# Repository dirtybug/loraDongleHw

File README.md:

# LoRa DualBand Hardware

R2 development draft. Not approved for manufacture. Hardware only; firmware and Android are separate submodules.

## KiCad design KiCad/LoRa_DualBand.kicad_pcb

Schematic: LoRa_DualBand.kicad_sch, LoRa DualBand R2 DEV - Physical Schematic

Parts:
C1A, C1B: 220u; C_1210_3225Metric; MPN GRM32ER60J227ME05L; not fitted
C2, C3, C4, C5, C6, C7, C9, C23, C25, C28, C35, C36, C37, C42, C44, C46, C48, C49, C50, C52, C53, C54, C55, C56, C59, C65, C66, C71, C73: 100n; C_0603_1608Metric; MPN CC0603KRX7R7BB104
C8, C32, C33, C34, C60, C63, C64: 1u; C_0603_1608Metric; MPN CC0603KRX7R6BB105
C10, C21, C38, C43, C45, C47, C51, C61: 4.7u; C_0603_1608Metric; MPN CC0603MRX5R6BB475
C20: 22n; C_0603_1608Metric; MPN CC0603KRX7R9BB223; not fitted
C22: 4.7u; C_0603_1608Metric; MPN CC0603MRX5R6BB475; not fitted
C24: 10u; C_0805_2012Metric; MPN GRM21BR61C106KE15L
C26, C27, C70, C72: 22u; C_0805_2012Metric; MPN GRM21BR61A226ME44L
C30, C31, C40, C41, C57, C58: 18p; C_0603_1608Metric; MPN CC0603JRNPO9BN180
C62: 1n; C_0603_1608Metric; MPN CC0603KRX7R9BB102
D1: USBLC6-2SC6; SOT-23-6; MPN USBLC6-2SC6
D2: SMAJ5.0A; D_SMA; MPN SMAJ5.0A
D3: SMAJ5.0A; D_SMA; MPN SMAJ5.0A; not fitted
FB1, FB2: 600R@100MHz; R_0805_2012Metric; MPN BLM21PG601SN1D
FB3, FB4: 600R@100MHz; R_0603_1608Metric; MPN BLM18PG601SN1D
FID1, FID2, FID3: Fiducial; Fiducial_1mm_Mask2mm
FL1: LFCN-490+; Filter_Mini-Circuits_FV1206; MPN LFCN-490+
FL2: HFCN-740+; Filter_Mini-Circuits_FV1206; MPN HFCN-740+
FL3: LFCN-900+; Filter_Mini-Circuits_FV1206; MPN LFCN-900+
J1: USB_C_PLUG; USB_C_Plug_JAE_DX07P024AJ1; MPN DX07P024AJ1
J2: SMA_433; SMA_Amphenol_132289_EdgeMount; MPN 132289
J3: SMA_868; SMA_Amphenol_132289_EdgeMount; MPN 132289
J4: CORTEX_SWD_10P; PinHeader_2x05_P1.27mm_Vertical_SMD; MPN FTSH-105-01-L-DV-K
J5: DEBUG_EN_JMP; PinHeader_1x02_P2.54mm_Vertical; MPN 61300211121
J6: AUX_USB_C; USB_C_Receptacle_HRO_TYPE-C-31-M-12; MPN TYPE-C-31-M-12; not fitted
J7: PROBE_SWD_5; PinHeader_1x05_P2.54mm_Vertical; MPN 61300511121
L1: 3.3uH; L_Vishay_IHLP-1616; MPN IHLP1616ABER3R3M01
LED1, LED4: GREEN; LED_0603_1608Metric; MPN LTST-C190KGKT
LED2: AMBER; LED_0603_1608Metric; MPN LTST-C190KFKT
LED3: BLUE; LED_0603_1608Metric; MPN LTST-C190TBKT
R1: 5.1k; R_0603_1608Metric; MPN RC0603FR-075K1L
R2, R3: 5.1k; R_0603_1608Metric; MPN RC0603FR-075K1L; not fitted
R4, R5, R6, R7, R8, R9, R10, R11, R13, R32, R38, R39, R40, R41, R42, R43, R45, R47, R48, R49: 10k; R_0603_1608Metric; MPN RC0603FR-0710KL
R20, R22, R24, R26: 100k; R_0603_1608Metric; MPN RC0603FR-07100KL; not fitted
R21, R23: 33.2k; R_0603_1608Metric; MPN RC0603FR-0733K2L; not fitted
R25, R27: 24.9k; R_0603_1608Metric; MPN RC0603FR-0724K9L; not fitted
R28: 15k; R_0603_1608Metric; MPN RC0603FR-0715KL; not fitted
R29, R30, R36, R37, R50, R54, R55, R56, R57: 100k; R_0603_1608Metric; MPN RC0603FR-07100KL
R31: 33.2k; R_0603_1608Metric; MPN RC0603FR-0733K2L
R33, R34, R51, R52, R53: 1k; R_0603_1608Metric; MPN RC0603FR-071KL
R35, R44: 12k; R_0603_1608Metric; MPN RC0603FR-0712KL
R46: 2.2k; R_0603_1608Metric; MPN RC0603FR-072K2L
R101, R102, R103, R104, R105, R106, R107, R108, R109, R110, R111, R112, R113, R114, R115, R116, R117, R118, R121, R122, R123, R124, R125, R126, R127, R128, R129, R131, R132, R133, R134, R135, R136, R137, R138, R139: 0R; R_0603_1608Metric; MPN RC0603JR-070RL
R_PWR_3V3: 0R; R_0805_2012Metric; MPN RC0805JR-070RL
R_PWR_U1, R_PWR_U2, R_PWR_U6, R_PWR_U7: 0R; R_0603_1608Metric; MPN RC0603JR-070RL
R_RF_A: 0R; R_0402_1005Metric; MPN RC0402JR-070RL
R_RF_B: 0R; R_0402_1005Metric; MPN RC0402JR-070RL
SJ1: BYPASS_BASIC; SolderJumper-2_P1.3mm_Bridged_Pad1.0x1.5mm
TP1: TP_VBUS; TestPoint_Pad_D1.0mm
TP2: TP_SYS_5V; TestPoint_Pad_D1.0mm
TP3: TP_U5_3V3_OUT; TestPoint_Pad_D1.0mm
TP4: TP_3V3; TestPoint_Pad_D1.0mm
TP5: TP_3V3_HUB; TestPoint_Pad_D1.0mm
TP6: TP_3V3_FTDI; TestPoint_Pad_D1.0mm
TP7: TP_3V3_MCU; TestPoint_Pad_D1.0mm
TP8: TP_3V3_RF433; TestPoint_Pad_D1.0mm
TP9: TP_3V3_RF868; TestPoint_Pad_D1.0mm
TP10: TP_DBG_3V3; TestPoint_Pad_D1.0mm
TP11: TP_3V3_PROBE; TestPoint_Pad_D1.0mm
TP12: TP_DEBUG_EN; TestPoint_Pad_D1.0mm
TP13, TP14, TP15, TP16: TP_GND; TestPoint_Pad_D1.0mm
U1: FT4232HL; LQFP-64_10x10mm_P0.5mm; MPN FT4232HL
U2: STM32G0B1RET6; LQFP-64_10x10mm_P0.5mm; MPN STM32G0B1RET6
U3: E22-400M22S; Ebyte_E22-M22S_14x20mm; MPN E22-400M22S
U4: E22-900M22S; Ebyte_E22-M22S_14x20mm; MPN E22-900M22S
U5: TPS562201DDCR; SOT-23-6; MPN TPS562201DDCR
U6: USB2422-I/MJ; QFN-24-1EP_4x4mm_P0.5mm_EP2.6x2.6mm; MPN USB2422-I/MJ
U7: STM32U073CCT6; LQFP-48_7x7mm_P0.5mm; MPN STM32U073CCT6
U8, U11: SN74CB3Q3126PWR; TSSOP-14_4.4x5mm_P0.65mm; MPN SN74CB3Q3126PWR
U9: TPS22918DBVR; SOT-23-6; MPN TPS22918DBVR
U10: TPS2121RUXR; TI_VQFN-HR-12_2.0x2.5mm_RUX; MPN TPS2121RUXR; not fitted
U12: 93LC56BT-I/SN; SOIC-8_3.9x4.9mm_P1.27mm; MPN 93LC56BT-I/SN
Y1: 12MHz; Crystal_SMD_3225-4Pin_3.2x2.5mm; MPN ABM8G-12.000MHZ-4Y-T3
Y2: 24MHz; Crystal_SMD_3225-4Pin_3.2x2.5mm; MPN ABM8G-24.000MHZ-4Y-T3
Y3: 16MHz; Crystal_SMD_3225-4Pin_3.2x2.5mm; MPN ABM8G-16.000MHZ-4Y-T3

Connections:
3V3: C63.1, C65.1, C66.1, FB1.1, FB2.1, LED1.2 (A), R29.2, R52.1, R_PWR_3V3.2, R_PWR_U1.1, R_PWR_U2.1, R_PWR_U6.1, TP4.1, U8.14 (VCC), U9.1 (VIN), U11.14 (VCC)
A_BUSY: R125.2, U3.14 (BUSY)
A_IRQ: R126.2, U3.13 (DIO1)
A_MISO: R122.2, U3.16 (MISO)
A_MOSI: R123.2, U3.17 (MOSI)
A_NSS: R5.1, R124.2, U3.19 (NSS)
A_SCK: R121.2, U3.18 (SCK)
BUCK_BST: C23.2, U5.6 (VBST)
BUCK_EN: R30.2, U5.5 (EN)
BUCK_FB: R31.2, R32.1, U5.4 (FB)
BUCK_SW: C23.1, L1.1, U5.2 (SW)
B_BUSY: R135.2, U4.14 (BUSY)
B_IRQ: R136.2, U4.13 (DIO1)
B_MISO: R132.2, U4.16 (MISO)
B_MOSI: R133.2, U4.17 (MOSI)
B_NSS: R6.1, R134.2, U4.19 (NSS)
B_SCK: R131.2, U4.18 (SCK)
CC: J1.A5 (CC), R1.1
CC1_EXT: J6.A5 (CC1), R2.1
CC2_EXT: J6.B5 (CC2), R3.1
CTRL_CTS: R104.1, U1.19 (ADBUS3)
CTRL_RTS: R103.1, U1.18 (ADBUS2)
CTRL_RX: R102.1, U1.17 (ADBUS1)
CTRL_TX: R101.1, U1.16 (ADBUS0)
DATA433_CTS: R108.1, U1.29 (BDBUS3)
DATA433_RTS: R107.1, U1.28 (BDBUS2)
DATA433_RX: R106.1, U1.27 (BDBUS1)
DATA433_TX: R105.1, U1.26 (BDBUS0)
DATA868_CTS: R112.1, U1.41 (CDBUS3)
DATA868_RTS: R111.1, U1.40 (CDBUS2)
DATA868_RX: R110.1, U1.39 (CDBUS1)
DATA868_TX: R109.1, U1.38 (CDBUS0)
DBG_3V3: C64.1, LED2.2 (A), R_PWR_U7.1, TP10.1, U9.5 (QOD), U9.6 (VOUT); also elsewhere on the board
DBG_LOG_RX: U7.13 (PA3), U11.5 (2A)
DBG_LOG_TX: U7.12 (PA2), U11.2 (1A)
DBG_NRST: U7.16 (PA6), U8.9 (3A)
DBG_SWCLK: U7.15 (PA5), U8.5 (2A)
DBG_SWDIO: U7.14 (PA4), U8.2 (1A)
FT_EECLK: R48.1, U1.62 (EECLK), U12.2 (SCLK)
FT_EECS: R47.1, U1.63 (EECS), U12.1 (CS)
FT_EEDATA: R46.1, R49.1, U1.61 (EEDATA), U12.3 (DI)
FT_EEDO: R46.2, U12.4 (DO)
FT_OSCI: C40.1, U1.2 (OSCI), Y1.1
FT_REF: R44.1, U1.6 (REF)
FT_RESET_N: C42.1, R45.1, U1.14 (~RESET)
FT_VPHY: C43.1, C44.1, FB3.2, U1.4 (VPHY)
FT_VPLL: C45.1, C46.1, FB4.2, U1.9 (VPLL)
HUB1_DM: U1.7 (DM), U6.2 (USBDM_DN1)
HUB1_DP: U1.8 (DP), U6.3 (USBDP_DN1)
HUB2_DM: U6.4 (USBDM_DN2), U7.32 (PA11)
HUB2_DP: U6.5 (USBDP_DN2), U7.33 (PA12)
HUB_CFG_SEL0: R42.1, U6.14 (CFG_SEL0)
HUB_CRFILT: C33.1, U6.10 (CRFILT)
HUB_NON_REM1: R41.1, U6.13 (NON_REM1)
HUB_OCS1_N: R39.1, U6.8 (OCS1_N)
HUB_OCS2_N: R40.1, U6.12 (OCS2_N)
HUB_RBIAS: R35.1, U6.24 (RBIAS)
HUB_RESET_N: C32.1, R38.1, U6.15 (RESET_N)
HUB_VBUS_DET: R36.2, R37.1, U6.16 (VBUS_DET)
HUB_XTALIN: C30.1, U6.22 (XTALIN), Y2.1
J5_3V3_LIM: J5.1, R52.2
LED1_K: LED1.1 (K), R33.1
LED2_K: LED2.1 (K), R34.1
LED3_K: LED3.1 (K), R51.1
LED4_K: LED4.1 (K), R53.1
LOG_RX: R118.1, U11.6 (2B)
LOG_TX: R117.1, U11.3 (1B)
MCU_OSC_IN: C57.1, U2.10 (PF0), Y3.1
MESH_CTS: R116.1, U1.54 (DDBUS3)
MESH_RTS: R115.1, U1.53 (DDBUS2)
MESH_RX: R114.1, U1.52 (DDBUS1)
MESH_TX: R113.1, U1.48 (DDBUS0)
MUX_CP2: R22.2, R23.1, U10.3 (CP2)
MUX_ILM: R28.1, U10.10 (ILM)
MUX_OV1: R24.2, R25.1, U10.5 (OV1)
MUX_OV2: R26.2, R27.1, U10.4 (OV2)
MUX_PR1: R20.2, R21.1, U10.6 (PR1)
MUX_SS: C20.1, U10.11 (SS)
M_A_BUSY: R125.1, U2.25 (PC4)
M_A_IRQ: R126.1, U2.26 (PC5)
M_A_MISO: R122.1, U2.23 (PA6)
M_A_MOSI: R123.1, U2.24 (PA7)
M_A_NSS: R124.1, U2.21 (PA4)
M_A_RESET: R127.1, U2.27 (PB0)
M_A_RXEN: R128.1, U2.28 (PB1)
M_A_SCK: R121.1, U2.22 (PA5)
M_A_TXEN: R129.1, U2.29 (PB2)
M_B_BUSY: R135.1, U2.40 (PD8)
M_B_IRQ: R136.1, U2.41 (PD9)
M_B_MISO: R132.1, U2.15 (PC2)
M_B_MOSI: R133.1, U2.16 (PC3)
M_B_NSS: R134.1, U2.50 (PD0)
M_B_RESET: R137.1, U2.48 (PC8)
M_B_RXEN: R138.1, U2.49 (PC9)
M_B_SCK: R131.1, U2.51 (PD1)
M_B_TXEN: R139.1, U2.64 (PC10)
M_CTRL_CTS: R104.2, U2.57 (PB3)
M_CTRL_RTS: R103.2, U2.58 (PB4)
M_CTRL_RX: R102.2, U2.60 (PB6)
M_CTRL_TX: R101.2, U2.61 (PB7)
M_DATA433_CTS: R108.2, U2.18 (PA1)
M_DATA433_RTS: R107.2, U2.17 (PA0)
M_DATA433_RX: R106.2, U2.19 (PA2)
M_DATA433_TX: R105.2, U2.20 (PA3)
M_DATA868_CTS: R112.2, U2.34 (PB14)
M_DATA868_RTS: R111.2, U2.33 (PB13)
M_DATA868_RX: R110.2, U2.30 (PB10)
M_DATA868_TX: R109.2, U2.31 (PB11)
M_LOG_RX: R118.2, U2.38 (PC6)
M_MESH_CTS: R116.2, U2.54 (PD4)
M_MESH_RTS: R115.2, U2.55 (PD5)
M_MESH_RX: R114.2, U2.53 (PD3)
M_MESH_TX: R113.2, U2.52 (PD2)
PROBE_BOOT0: R13.1, U7.44 (PF3-BOOT0)
PROBE_SWCLK: J7.2, U7.37 (PA14)
PROBE_SWDIO: J7.4, U7.34 (PA13)
PWR_SRC_ST: R29.1, U2.13 (PC0), U10.9 (ST)
RF_A: J2.1 (In), R_RF_A.2
RF_A_FILT: FL1.3 (OUT), R_RF_A.1
RF_A_MOD: FL1.1 (IN), U3.21 (ANT)
RF_B: J3.1 (In), R_RF_B.2
RF_B_FILT: FL3.3 (OUT), R_RF_B.1
RF_B_MID: FL2.3 (OUT), FL3.1 (IN)
RF_B_MOD: FL2.1 (IN), U4.21 (ANT)
SYS_5V: C1A.1, C1B.1, C24.1, C25.1, R30.1, SJ1.2 (B), TP2.1, U5.3 (VIN), U10.1 (OUT), U10.8 (OUT)
U5_3V3_OUT: C26.1, C27.1, C28.1, L1.2, R31.1, R_PWR_3V3.1, TP3.1
U9_CT: C62.1, U9.4 (CT)
USB_DM: D1.4 (I/O2), U6.19 (USBDM_UP)
USB_DM_CON: D1.3 (I/O2), J1.A7 (D-)
USB_DP: D1.6 (I/O1), U6.20 (USBDP_UP)
USB_DP_CON: D1.1 (I/O1), J1.A6 (D+)
USB_PWREN_N: U1.60 (~PWREN), U2.14 (PC1)
USB_SUSP: R43.1, U2.3 (PC13), U6.17 (SUSP_IND)
VBUS: C21.1, D1.5 (VBUS), D2.1 (A1), J1.A4 (VBUS), J1.A9 (VBUS), J1.B4 (VBUS), J1.B9 (VBUS), R22.1, R26.1, R36.1, SJ1.1 (A), TP1.1, U10.2 (IN2)
VBUS_EXT: C22.1, D3.1 (A1), J6.A4 (VBUS), J6.A9 (VBUS), J6.B4 (VBUS), J6.B9 (VBUS), R20.1, R24.1, U10.7 (IN1)

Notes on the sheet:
ZONE A: USB-C MAIN (J1), AUX USB-C (J6), ESD/TVS, TPS2121 POWER MUX (U10), BUCK 3.3V (U5) & 0R POWER LINKS
ZONE B: USB 2.0 HI-SPEED HUB (U6 USB2422) & 24 MHz CRYSTAL
ZONE C: QUAD USB-UART BRIDGE (U1 FT4232HL), 12 MHz CRYSTAL, 93LC56BT EEPROM & 16x 0R UART ISOLATION
ZONE D: MAIN MCU (U2 STM32G0B1RET6), 16 MHz HSE CRYSTAL & CORTEX 10-PIN SWD (J4)
ZONE E: ONBOARD DEBUGGER (U7 STM32U073CCT6), LOAD SWITCH (U9), SWD/UART ISOLATION (U8/U11) & J5/J7
ZONE F: 433 MHz LORA RADIO (U3 E22-400M22S), SMA (J2) & 9x 0R ISOLATION LINKS
ZONE G: 868 MHz LORA RADIO (U4 E22-900M22S), SMA (J3) & 9x 0R ISOLATION LINKS
ZONE H: BENCH TEST POINTS (TP1..TP16) & OPTICAL FIDUCIALS (FID1..FID3)

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
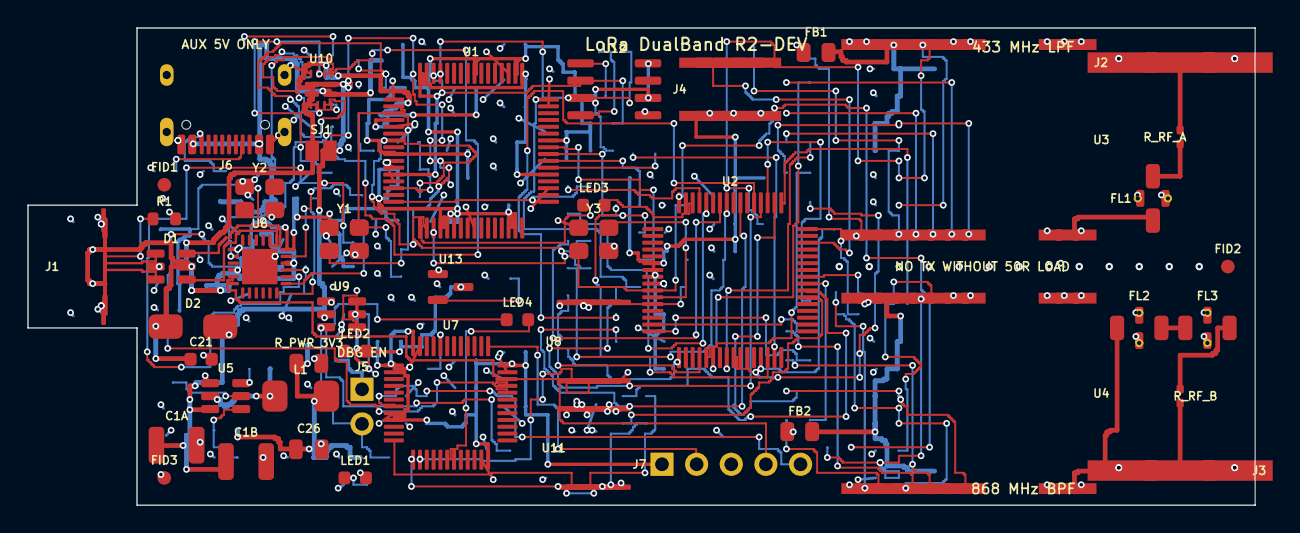
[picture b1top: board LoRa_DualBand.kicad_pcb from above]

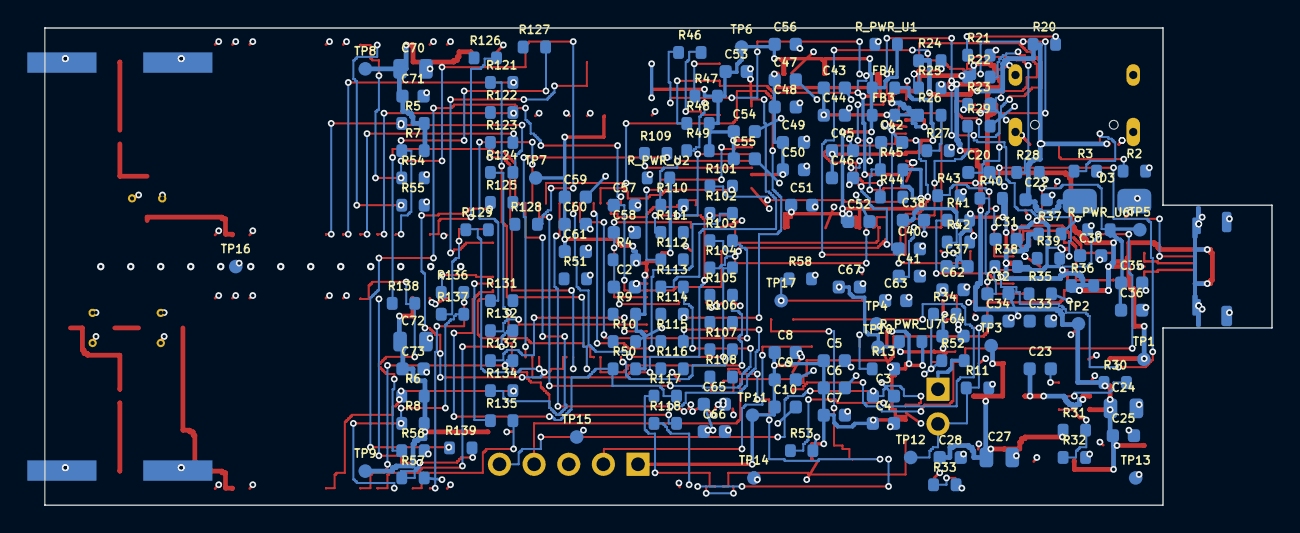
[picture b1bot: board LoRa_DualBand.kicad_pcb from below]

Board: 4 copper layers, 90.0 x 35.0 mm, 214 parts (167 on the bottom side), 162 nets.

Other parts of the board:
C67: 100n; C_0603_1608Metric
R58: 100k; R_0603_1608Metric
TP17: TP_DBG_BUS_EN; TestPoint_Pad_D1.0mm
U13: TPS3839K33DBZR; SOT-23

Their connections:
DBG_3V3: C67.1, U13.3; also elsewhere on the board

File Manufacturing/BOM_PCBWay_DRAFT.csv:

Line#,Designator,Qty,Manufacturer Part Number,Manufacturer,Description,Package,Type,Basic,Full,Status
1,J1,1,DX07P024AJ1,JAE,USB-C male plug 1.6mm (USB_C_PLUG),USB-C-Plug,SMD,Fit,Fit,DEV-Ready
2,R1,1,RC0603FR-075K1L,Yageo,5.1k USB-C plug Rd (CC) (5.1k),0603,SMD,Fit,Fit,DEV-Ready
3,D1,1,USBLC6-2SC6,STMicroelectronics,USB 2.0 HS ESD protection <1pF (USBLC6-2SC6),SOT-23-6,SMD,Fit,Fit,DEV-Ready
4,D2,1,SMAJ5.0A,Littelfuse,5V TVS diode VBUS hot-plug protection (SMAJ5.0A),SMA,SMD,Fit,Fit,DEV-Ready
5,J6,1,TYPE-C-31-M-12,HRO,USB-C auxiliary 5V input receptacle (AUX_USB_C),USB-C-16P,SMD,DNP,Fit,DEV-Ready
6,"R2,R3",2,RC0603FR-075K1L,Yageo,5.1k Aux USB-C CC1 Rd (5.1k),0603,SMD,DNP,Fit,DEV-Ready
7,D3,1,SMAJ5.0A,Littelfuse,5V TVS diode VBUS_EXT protection (SMAJ5.0A),SMA,SMD,DNP,Fit,DEV-Ready
8,U10,1,TPS2121RUXR,Texas Instruments,2.8-22V 4.5A Priority Power Mux (TPS2121RUXR),VQFN-HR-12,SMD,DNP,Fit,DEV-Ready
9,SJ1,1,,PCB,Power mux bypass (Closed Basic; Open Full) (BYPASS_BASIC),SolderJumper,PCB,Fit,DNP,DEV-Ready
10,"R20,R22,R24,R26",4,RC0603FR-07100KL,Yageo,TPS2121 PR1 divider top (100k),0603,SMD,DNP,Fit,DEV-Ready
11,"R21,R23",2,RC0603FR-0733K2L,Yageo,TPS2121 PR1 divider bottom (33.2k),0603,SMD,DNP,Fit,DEV-Ready
12,"R25,R27",2,RC0603FR-0724K9L,Yageo,TPS2121 OV1 bottom (24.9k),0603,SMD,DNP,Fit,DEV-Ready
13,R28,1,RC0603FR-0715KL,Yageo,TPS2121 ILIM ~1.5A limit (15k),0603,SMD,DNP,Fit,DEV-Ready
14,"R29,R30,R36,R37,R50,R54,R55,R56,R57",9,RC0603FR-07100KL,Yageo,TPS2121 ST open-drain pull-up (100k),0603,SMD,Fit,Fit,DEV-Ready
15,C20,1,CC0603KRX7R9BB223,Yageo,TPS2121 SS soft-start cap (22n),0603,SMD,DNP,Fit,DEV-Ready
16,"C21,C38,C43,C45,C47,C51,C61,C10",8,CC0603MRX5R6BB475,Yageo,VBUS input cap <=10uF USB spec (4.7u),0603,SMD,Fit,Fit,DEV-Ready
17,C22,1,CC0603MRX5R6BB475,Yageo,VBUS_EXT input cap (4.7u),0603,SMD,DNP,Fit,DEV-Ready
18,"C1A,C1B",2,GRM32ER60J227ME05L,Murata,220uF bulk reservoir 1/2 (440uF total after inrush) (220u),1210,SMD,DNP,Fit,DEV-Ready
19,U5,1,TPS562201DDCR,Texas Instruments,4.5-17V 2A Sync Step-Down Buck (TPS562201DDCR),SOT-23-6,SMD,Fit,Fit,DEV-Ready
20,L1,1,IHLP1616ABER3R3M01,Vishay,3.3uH 3.5A shielded power inductor (3.3uH),4040,SMD,Fit,Fit,DEV-Ready
21,R31,1,RC0603FR-0733K2L,Yageo,TPS562201 FB top (3.31V) (33.2k),0603,SMD,Fit,Fit,DEV-Ready
22,"R32,R38,R39,R40,R41,R42,R43,R45,R47,R48,R49,R4,R9,R10,R11,R13,R5,R7,R6,R8",20,RC0603FR-0710KL,Yageo,TPS562201 FB bottom (10k),0603,SMD,Fit,Fit,DEV-Ready
23,"C23,C25,C28,C35,C36,C37,C42,C44,C46,C48,C49,C50,C52,C53,C54,C55,C56,C2,C59,C65,C66,C3,C4,C5,C6,C7,C9,C71,C73",29,CC0603KRX7R7BB104,Yageo,TPS562201 VBST bootstrap (100n),0603,SMD,Fit,Fit,DEV-Ready
24,C24,1,GRM21BR61C106KE15L,Murata,TPS562201 VIN bulk cap 16V (10u),0805,SMD,Fit,Fit,DEV-Ready
25,"C26,C27,C70,C72",4,GRM21BR61A226ME44L,Murata,TPS562201 VOUT bulk 1 (22u),0805,SMD,Fit,Fit,DEV-Ready
26,R_PWR_3V3,1,RC0805JR-070RL,Yageo,0R link U5_3V3_OUT -> 3V3 (0R),0805,SMD,Fit,Fit,DEV-Ready
27,"R_PWR_U6,R_PWR_U1,R_PWR_U2,R_PWR_U7,R101,R102,R103,R104,R105,R106,R107,R108,R109,R110,R111,R112,R113,R114,R115,R116,R117,R118,R121,R122,R123,R124,R125,R126,R127,R128,R129,R131,R132,R133,R134,R135,R136,R137,R138,R139",40,RC0603JR-070RL,Yageo,0R link 3V3 -> 3V3_HUB (0R),0603,SMD,Fit,Fit,DEV-Ready
28,"FB1,FB2",2,BLM21PG601SN1D,Murata,RF 433MHz power ferrite / isolation (600R@100MHz),0805,SMD,Fit,Fit,DEV-Ready
29,"LED1,LED4",2,LTST-C190KGKT,Lite-On,3V3 Power ON LED (GREEN),0603,SMD,Fit,Fit,DEV-Ready
30,"R33,R34,R51,R52,R53",5,RC0603FR-071KL,Yageo,LED1 current limit (1k),0603,SMD,Fit,Fit,DEV-Ready
31,LED2,1,LTST-C190KFKT,Lite-On,DBG_3V3 Debugger ON LED (AMBER),0603,SMD,Fit,Fit,DEV-Ready
32,U6,1,USB2422-I/MJ,Microchip,2-Port USB 2.0 Hi-Speed Hub (USB2422-I/MJ),QFN-24,SMD,Fit,Fit,DEV-Ready
33,Y2,1,ABM8G-24.000MHZ-4Y-T3,Abracon,24MHz crystal for USB2422 (24MHz),3225,SMD,Fit,Fit,DEV-Ready
34,"C30,C31,C40,C41,C57,C58",6,CC0603JRNPO9BN180,Yageo,Y2 24MHz load cap 1 C0G (18p),0603,SMD,Fit,Fit,DEV-Ready
35,"R35,R44",2,RC0603FR-0712KL,Yageo,USB2422 RBIAS 12.0k 1% (12k),0603,SMD,Fit,Fit,DEV-Ready
36,"C32,C33,C34,C60,C63,C64,C8",7,CC0603KRX7R6BB105,Yageo,USB2422 RESET_N RC cap (1u),0603,SMD,Fit,Fit,DEV-Ready
37,U1,1,FT4232HL,FTDI,Quad Hi-Speed USB to UART (FT4232HL),LQFP-64,SMD,Fit,Fit,DEV-Ready
38,Y1,1,ABM8G-12.000MHZ-4Y-T3,Abracon,12MHz crystal for FT4232HL (12MHz),3225,SMD,Fit,Fit,DEV-Ready
39,"FB3,FB4",2,BLM18PG601SN1D,Murata,FT4232HL VPHY ferrite (600R@100MHz),0603,SMD,Fit,Fit,DEV-Ready
40,U12,1,93LC56BT-I/SN,Microchip,2Kbit EEPROM for FT4232HL (93LC56BT-I/SN),SOIC-8,SMD,Fit,Fit,DEV-Ready
41,R46,1,RC0603FR-072K2L,Yageo,FT4232HL EEDATA-DO series (2.2k),0603,SMD,Fit,Fit,DEV-Ready
42,U2,1,STM32G0B1RET6,STMicroelectronics,Arm Cortex-M0+ 512KB Flash MCU (STM32G0B1RET6),LQFP-64,SMD,Fit,Fit,DEV-Ready
43,Y3,1,ABM8G-16.000MHZ-4Y-T3,Abracon,16MHz HSE crystal for STM32G0B1RET6 (16MHz),3225,SMD,Fit,Fit,DEV-Ready
44,LED3,1,LTST-C190TBKT,Lite-On,U2 MCU Heartbeat LED (BLUE),0603,SMD,Fit,Fit,DEV-Ready
45,J4,1,FTSH-105-01-L-DV-K,Samtec,ARM Cortex Debug 10-pin 1.27mm keyed (CORTEX_SWD_10P),2x5-1.27mm,SMD,Fit,Fit,DEV-Ready
46,U9,1,TPS22918DBVR,Texas Instruments,5.5V 2A Load Switch active-high ON (TPS22918DBVR),SOT-23-6,SMD,Fit,Fit,DEV-Ready
47,C62,1,CC0603KRX7R9BB102,Yageo,U9 CT soft-start slew cap (1n),0603,SMD,Fit,Fit,DEV-Ready
48,J5,1,61300211121,Wurth,Debugger enable 2-pin jumper (DEBUG_EN_JMP),1x2-2.54mm,THT,Fit,Fit,DEV-Ready
49,"U8,U11",2,SN74CB3Q3126PWR,Texas Instruments,Quad FET Bus Switch SWD isolation (SN74CB3Q3126PWR),TSSOP-14,SMD,Fit,Fit,DEV-Ready
50,U7,1,STM32U073CCT6,STMicroelectronics,Ultra-Low-Power MCU USB FS Debugger (STM32U073CCT6),LQFP-48,SMD,Fit,Fit,DEV-Ready
51,J7,1,61300511121,Wurth,Probe SWD 5-pin ST-Link header (PROBE_SWD_5),1x5-2.54mm,THT,Fit,Fit,DEV-Ready
52,U3,1,E22-400M22S,Ebyte,SX1268 433MHz 22dBm TCXO LoRa module (E22-400M22S),14x20mm,SMD,Fit,Fit,DEV-Ready
53,FL1,1,LFCN-490+,Mini-Circuits,433MHz LTCC LPF DC-490MHz 8.5W (>35dB @ 868MHz) (LFCN-490+),FV1206,SMD,Fit,Fit,DEV-Ready
54,"R_RF_A,R_RF_B",2,RC0402JR-070RL,Yageo,433MHz RF 50-ohm series isolation/tuning (0R),0402,SMD,Fit,Fit,DEV-Ready
55,J2,1,132289,Amphenol,SMA female 50-ohm edge-launch TOP edge (433MHz) (SMA_433),SMA-Edge,SMD,Fit,Fit,DEV-Ready
56,U4,1,E22-900M22S,Ebyte,SX1262 868MHz 22dBm TCXO LoRa module (E22-900M22S),14x20mm,SMD,Fit,Fit,DEV-Ready
57,FL2,1,HFCN-740+,Mini-Circuits,868MHz LTCC HPF 780-2800MHz 7W (>40dB @ 433MHz) (HFCN-740+),FV1206,SMD,Fit,Fit,DEV-Ready
58,FL3,1,LFCN-900+,Mini-Circuits,868MHz LTCC LPF DC-900MHz 10W (>30dB @ 1736MHz) (LFCN-900+),FV1206,SMD,Fit,Fit,DEV-Ready
59,J3,1,132289,Amphenol,SMA female 50-ohm edge-launch BOTTOM edge (868MHz) (SMA_868),SMA-Edge,SMD,Fit,Fit,DEV-Ready
